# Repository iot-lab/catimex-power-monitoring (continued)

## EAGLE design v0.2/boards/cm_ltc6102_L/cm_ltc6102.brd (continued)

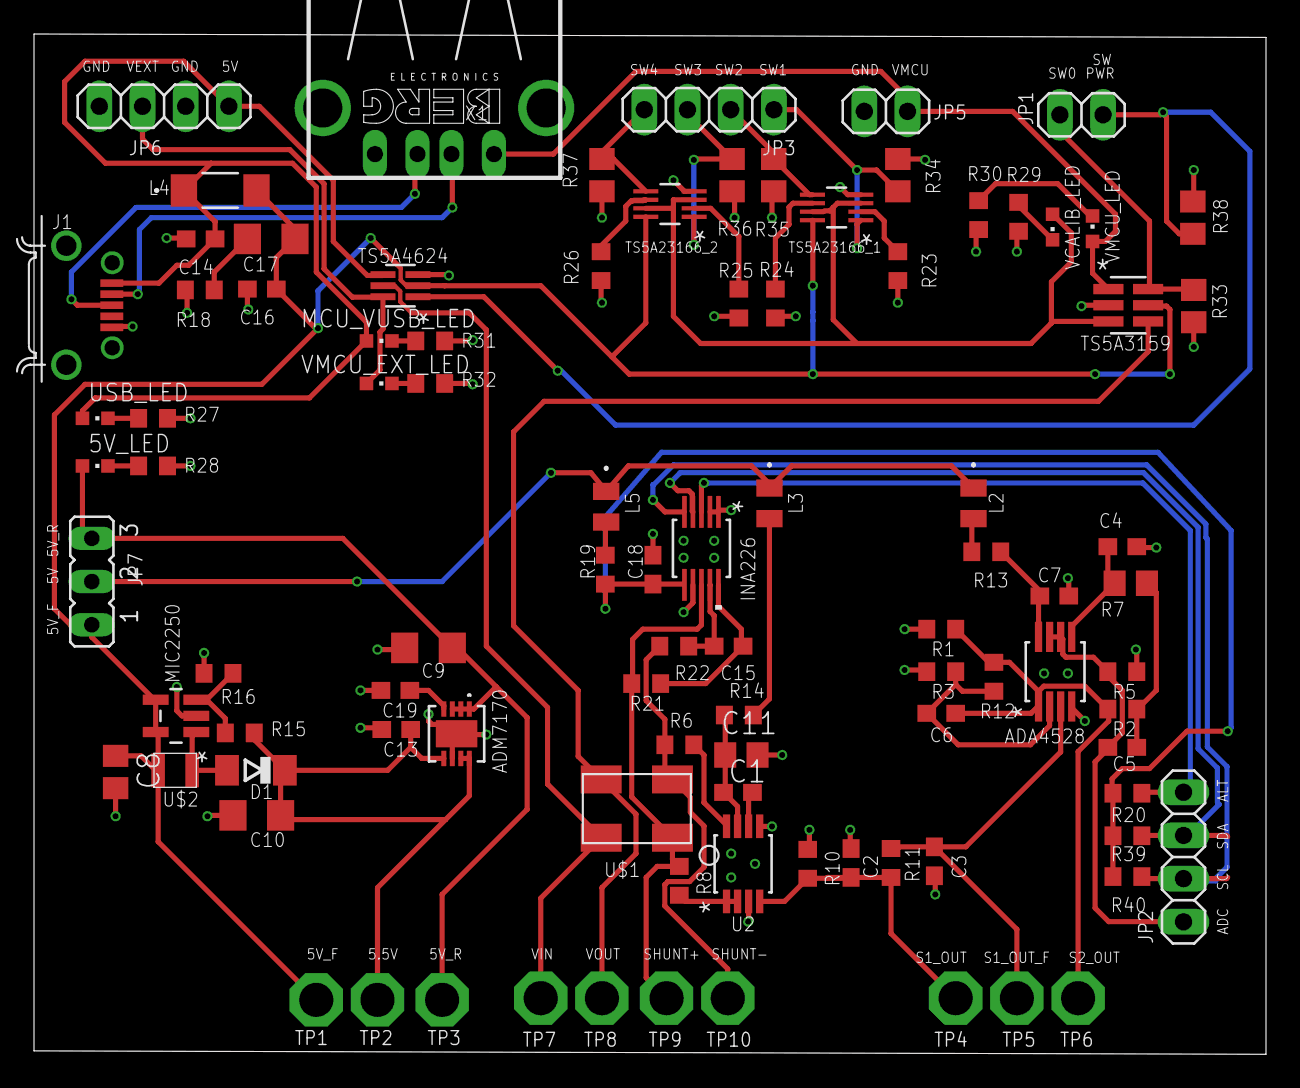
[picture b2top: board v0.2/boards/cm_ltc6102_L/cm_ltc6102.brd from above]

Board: 2 copper layers, 72.5 x 60.0 mm, 96 parts (1 on the bottom side), 57 nets.

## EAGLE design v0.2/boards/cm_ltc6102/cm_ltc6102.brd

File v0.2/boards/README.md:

# PCB eagle for current measurement board

This board contains the eagle files for current measurement board. It contains two options for the circuit:

* LTC6102 based circuit measurement
* ADA4522 based circuit measurement

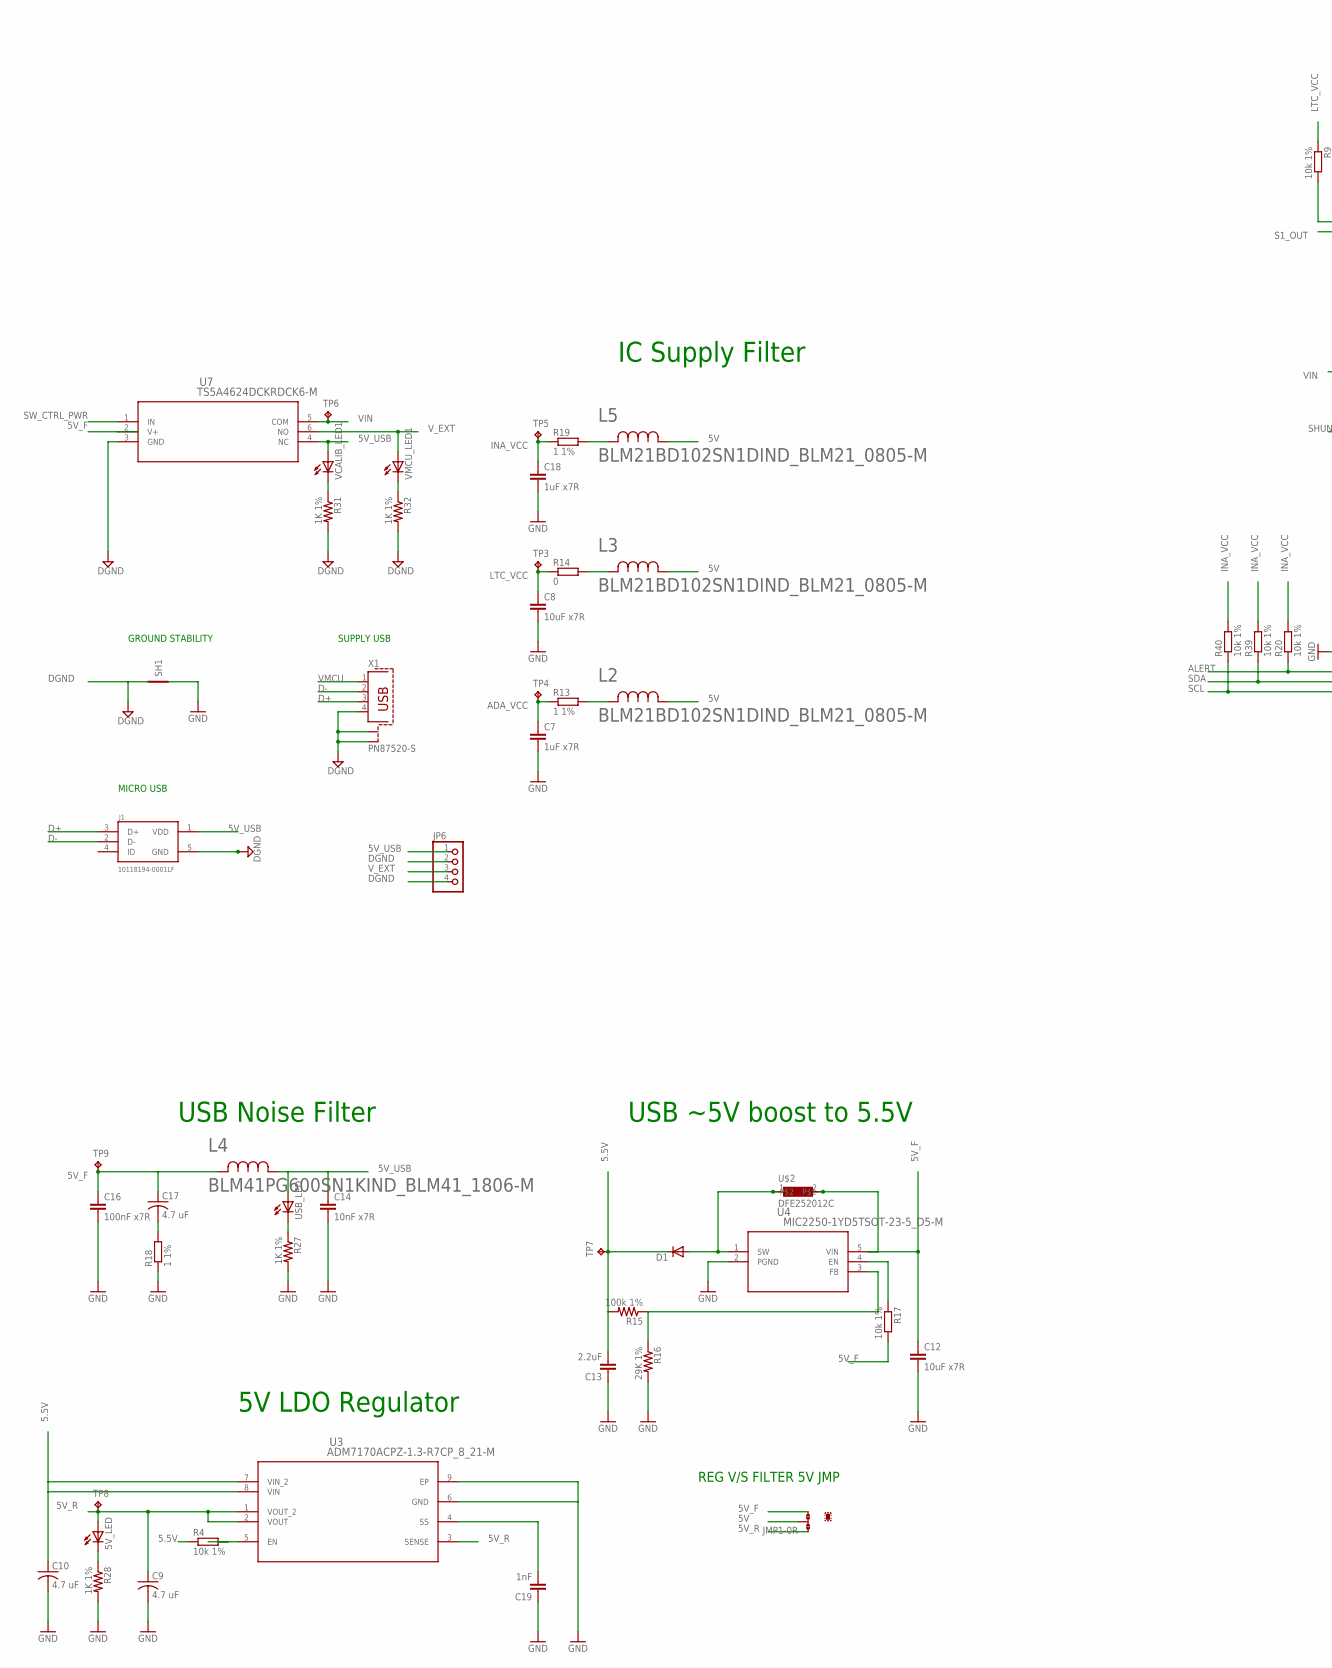
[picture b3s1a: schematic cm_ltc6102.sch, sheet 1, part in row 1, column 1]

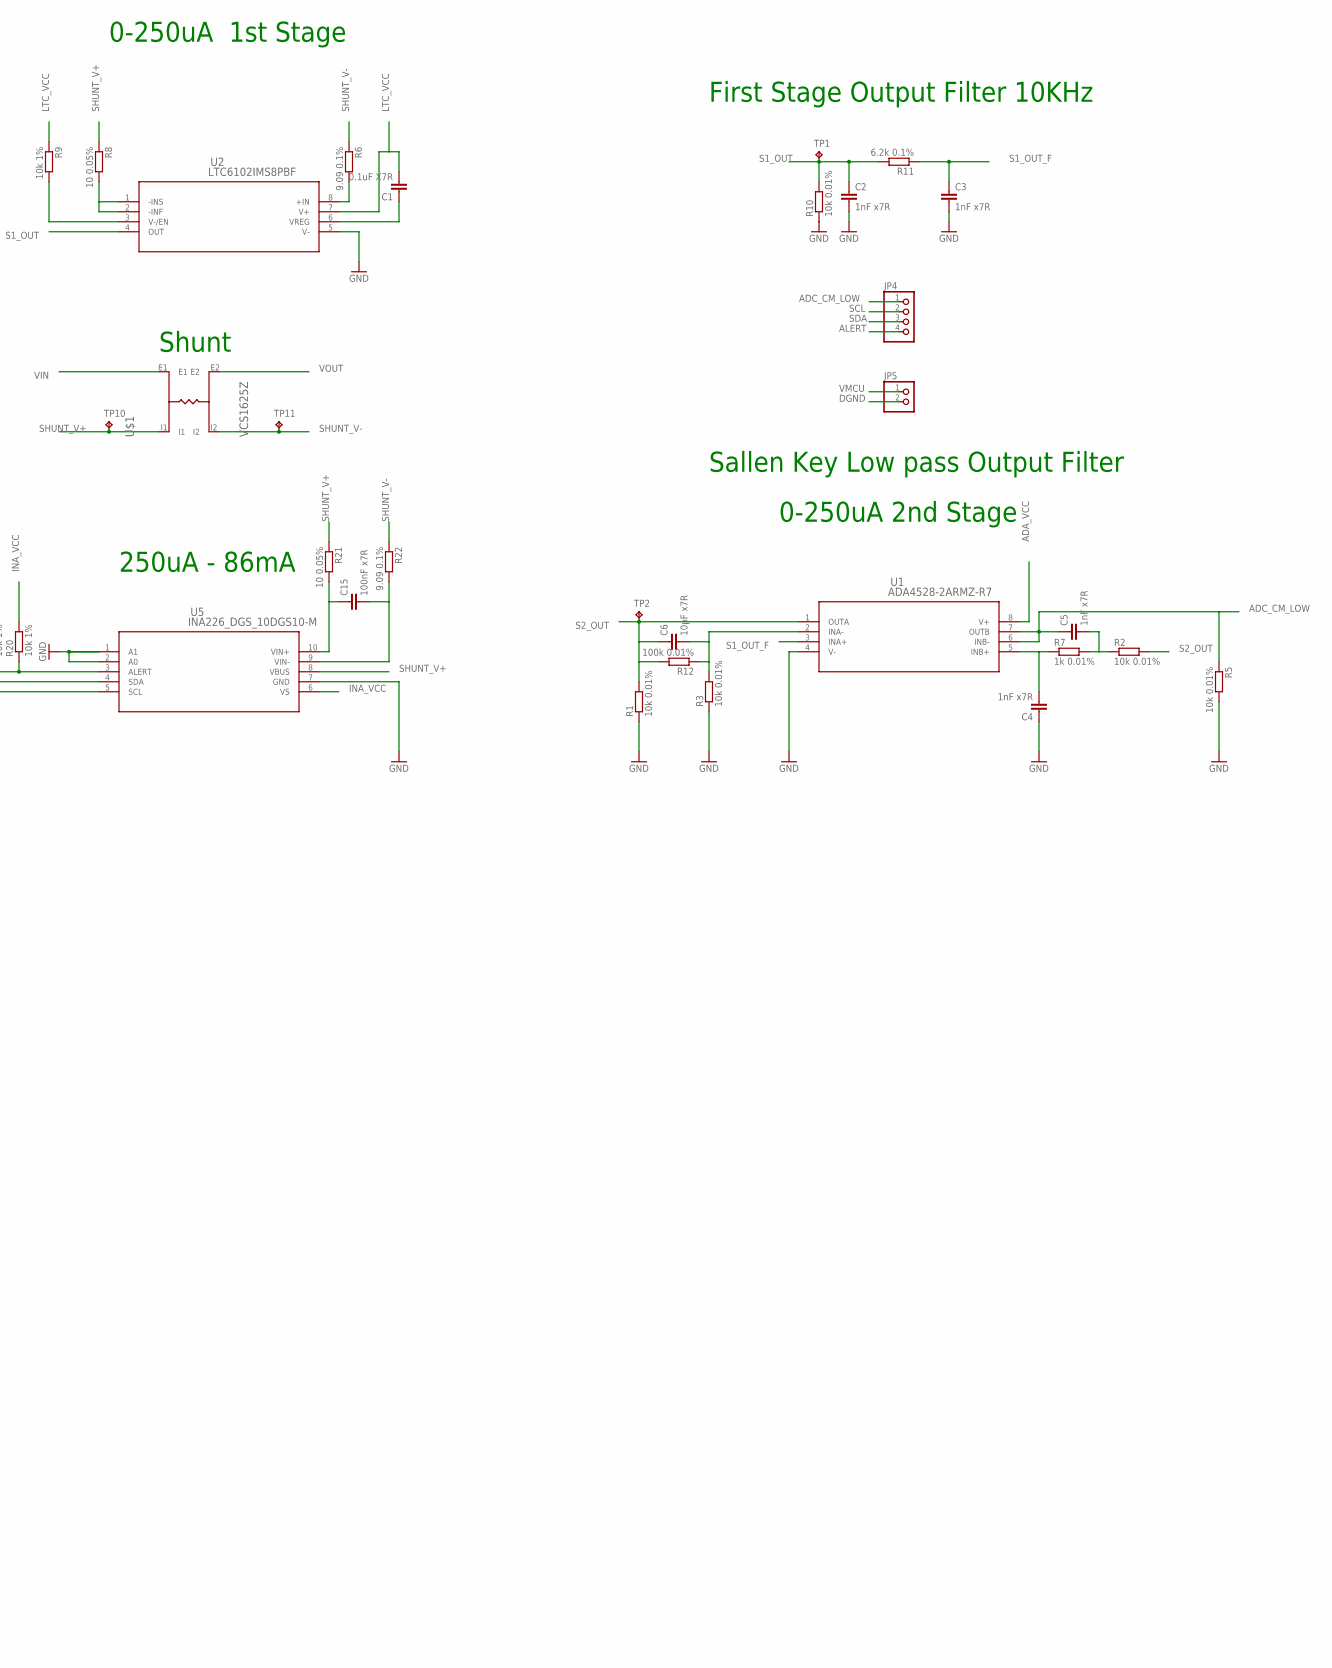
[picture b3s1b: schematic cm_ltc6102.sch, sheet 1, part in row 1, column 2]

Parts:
5V_LED: LEDCHIPLED_0603; CHIPLED_0603
C1: 0.1uF X7R; C0805
C2, C3, C4, C5: 1nF x7R; C0603
C6: 10pF x7R; C0603
C7, C18: 1uF x7R; C0603
C8, C12: 10uF x7R; C0603
C9, C10, C17: 4.7 uF; C1206
C13: 2.2uF; C0603
C14: 10nF x7R; C0603
C15, C16: 100nF x7R; C0603
C19: 1nF; C0603
D1: DIODE-SOD80C; SOD80C
J1: 10118194-0001LF; FRAMATOME_10118194-0001LF
JMP1: 0R-JUMPA; A0R-JMP
JP4, JP6: PINHD-1X4; 1X04
JP5: PINHD-1X2; 1X02
L2, L3, L5: BLM21BD102SN1DIND_BLM21_0805-M; IND_BLM21_0805-M
L4: BLM41PG600SN1KIND_BLM41_1806-M; IND_BLM41_1806-M
R1, R2, R3, R5, R10: 10k 0.01%; R0603
R4, R9, R17, R20, R39, R40: 10k 1%; R0603
R6, R22: 9.09 0.1%; R0603
R7: 1k 0.01%; R0805
R8, R21: 10 0.05%; R0603
R11: 6.2k 0.1%; R0603
R12: 100k 0.01%; R0603
R13, R18, R19: 1 1%; R0603
R14: 0; R0603
R15: 100k 1%; R0603
R16: 29K 1%; R0603
R27, R28, R31, R32: 1K 1%; R0603
SH1: SHORT-VT5; SHORT_TOP-50
TP1, TP2: TPPAD1-13; P1-13
TP3, TP4, TP5, TP6, TP7, TP8, TP9, TP10, TP11: TPTP11R; TP11R
U1: ADA4528-2ARMZ-R7; RM_8
U2: LTC6102IMS8PBF; MSOP-8_MS
U3: ADM7170ACPZ-1.3-R7CP_8_21-M; CP_8_21-M
U4: MIC2250-1YD5TSOT-23-5_D5-M; TSOT-23-5_D5-M
U5: INA226_DGS_10DGS10-M; DGS10-M
U7: TS5A4624DCKRDCK6-M; DCK6-M
U$1: VCS1625Z
U$2: DFE252012C
USB_LED: LEDCHIPLED_0603; CHIPLED_0603
VCALIB_LED1: LEDCHIPLED_0603; CHIPLED_0603
VMCU_LED1: LEDCHIPLED_0603; CHIPLED_0603
X1: PN87520-S

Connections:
5.5V: C10.1, C13.2, D1.C, R4.1, R15.2, TP7.TP, U3.7 (VIN_2), U3.8 (VIN)
5V: JMP1.2, L2.1, L3.1, L5.1
5V_F: C12.1, C16.1, C17.1, JMP1.3, L4.2, R17.2, TP9.TP, U4.5 (VIN), U7.2 (V+), U$2.2; also elsewhere on the board
5V_R: 5V_LED.A, C9.1, JMP1.1, TP8.TP, U3.1 (VOUT_2), U3.2 (VOUT), U3.3 (SENSE)
5V_USB: C14.1, J1.1 (VDD), JP6.1, L4.1, U7.4 (NC), USB_LED.A, VCALIB_LED1.A
ADA_VCC: C7.1, R13.1, TP4.TP, U1.8 (V+)
ADC_CM_LOW: C5.1, JP4.1, R5.1, U1.6 (INB-), U1.7 (OUTB)
ALERT: JP4.4, R20.1, U5.3 (ALERT)
D+: J1.3 (D+), X1.3
D-: J1.2 (D-), X1.2
DGND: J1.5 (GND), JP5.2, JP6.2, JP6.4, R31.2, R32.2, SH1.2, U7.3 (GND), X1.4, X1.S1, X1.S2; also elsewhere on the board
GND: C2.2, C3.2, C4.1, C7.2, C8.2, C9.2, C10.2, C12.2, C13.1, C14.2, C16.2, C18.2, C19.1, R1.1, R3.1, R5.2, R10.1, R16.2, R18.1, R27.2, R28.2, SH1.1, U1.4 (V-), U2.5 (V-), U3.6 (GND), U3.9 (EP), U4.2 (PGND), U5.1 (A1), U5.2 (A0), U5.7 (GND)
INA_VCC: C18.1, R19.1, R20.2, R39.2, R40.2, TP5.TP, U5.6 (VS)
LTC_VCC: C1.2, C8.1, R9.1, R14.1, TP3.TP, U2.7 (V+)
unnamed: R8.2, U2.1 (-INS), U2.2 (-INF)
unnamed: R6.2, U2.8 (+IN)
unnamed: R27.1, USB_LED.C
unnamed: R9.2, U2.3 (V-/EN)
unnamed: C1.1, U2.6 (VREG)
unnamed: C4.2, R7.1, U1.5 (INB+)
unnamed: C5.2, R2.1, R7.2
unnamed: L3.2, R14.2
unnamed: D1.A, U4.1 (SW), U$2.1
unnamed: C6.2, R3.2, R12.1, U1.2 (INA-)
unnamed: L2.2, R13.2
unnamed: C15.1, R21.2, U5.10 (VIN+)
unnamed: C19.2, U3.4 (SS)
unnamed: R4.2, U3.5 (EN)
unnamed: R15.1, R16.1, U4.3 (FB)
unnamed: R17.1, U4.4 (EN)
unnamed: C17.2, R18.2
unnamed: L5.2, R19.2
unnamed: C15.2, R22.2, U5.9 (VIN-)
unnamed: 5V_LED.C, R28.1
unnamed: R31.1, VCALIB_LED1.C
unnamed: R32.1, VMCU_LED1.C
S1_OUT: C2.1, R10.2, R11.2, TP1.TP, U2.4 (OUT)
S1_OUT_F: C3.1, R11.1, U1.3 (INA+)
S2_OUT: C6.1, R1.2, R2.2, R12.2, TP2.TP, U1.1 (OUTA)
SCL: JP4.2, R40.1, U5.5 (SCL)
SDA: JP4.3, R39.1, U5.4 (SDA)
SHUNT_V+: R8.1, R21.1, TP10.TP, U5.8 (VBUS), U$1.I1
SHUNT_V-: R6.1, R22.1, TP11.TP, U$1.I2
SW_CTRL_PWR: U7.1 (IN); also elsewhere on the board
VIN: TP6.TP, U7.5 (COM), U$1.E1
VMCU: JP5.1, X1.1; also elsewhere on the board
VOUT: U$1.E2; also elsewhere on the board
V_EXT: JP6.3, U7.6 (NO), VMCU_LED1.A

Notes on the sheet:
USB Noise Filter
USB ~5V boost to 5.5V
5V LDO Regulator
IC Supply Filter
First Stage Output Filter 10KHz
Sallen Key Low pass Output Filter
0-250uA 2nd Stage
0-250uA 1st Stage
250uA - 86mA
Shunt
SUPPLY USB
MICRO USB
GROUND STABILITY
REG V/S FILTER 5V JMP

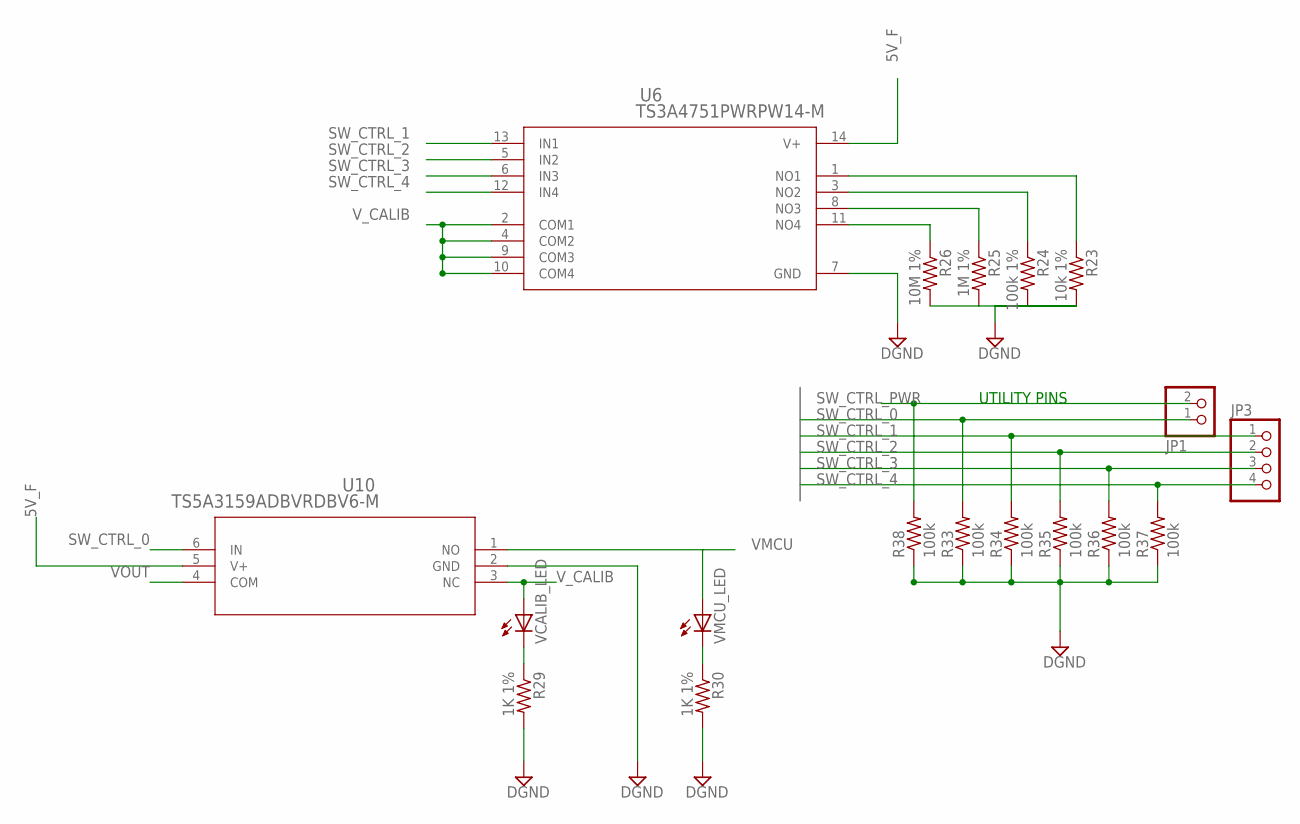
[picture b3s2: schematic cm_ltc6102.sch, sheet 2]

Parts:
JP1: PINHD-1X2; 1X02
JP3: PINHD-1X4; 1X04
R23: 10k 1%; R0603
R24: 100k 1%; R0603
R25: 1M 1%; R0603
R26: 10M 1%; R0603
R29, R30: 1K 1%; R0603
R33, R34, R35, R36, R37, R38: 100k; R0805
U6: TS3A4751PWRPW14-M; PW14-M
U10: TS5A3159ADBVRDBV6-M; DBV6-M
VCALIB_LED: LEDCHIPLED_0603; CHIPLED_0603
VMCU_LED: LEDCHIPLED_0603; CHIPLED_0603

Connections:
5V_F: U6.14 (V+), U10.5 (V+); also elsewhere on the board
DGND: R23.2, R24.2, R25.2, R26.2, R29.2, R30.2, R33.1, R34.1, R35.1, R36.1, R37.1, R38.1, U6.7 (GND), U10.2 (GND); also elsewhere on the board
unnamed: R29.1, VCALIB_LED.C
unnamed: R30.1, VMCU_LED.C
unnamed: R23.1, U6.1 (NO1)
unnamed: R24.1, U6.3 (NO2)
unnamed: R25.1, U6.8 (NO3)
unnamed: R26.1, U6.11 (NO4)
SW_CTRL_0: JP1.1, R33.2, U10.6 (IN)
SW_CTRL_1: JP3.1, R34.2, U6.13 (IN1)
SW_CTRL_2: JP3.2, R35.2, U6.5 (IN2)
SW_CTRL_3: JP3.3, R36.2, U6.6 (IN3)
SW_CTRL_4: JP3.4, R37.2, U6.12 (IN4)
SW_CTRL_PWR: JP1.2, R38.2; also elsewhere on the board
VMCU: U10.1 (NO), VMCU_LED.A; also elsewhere on the board
VOUT: U10.4 (COM); also elsewhere on the board
V_CALIB: U6.2 (COM1), U6.4 (COM2), U6.9 (COM3), U6.10 (COM4), U10.3 (NC), VCALIB_LED.A

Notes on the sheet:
UTILITY PINS

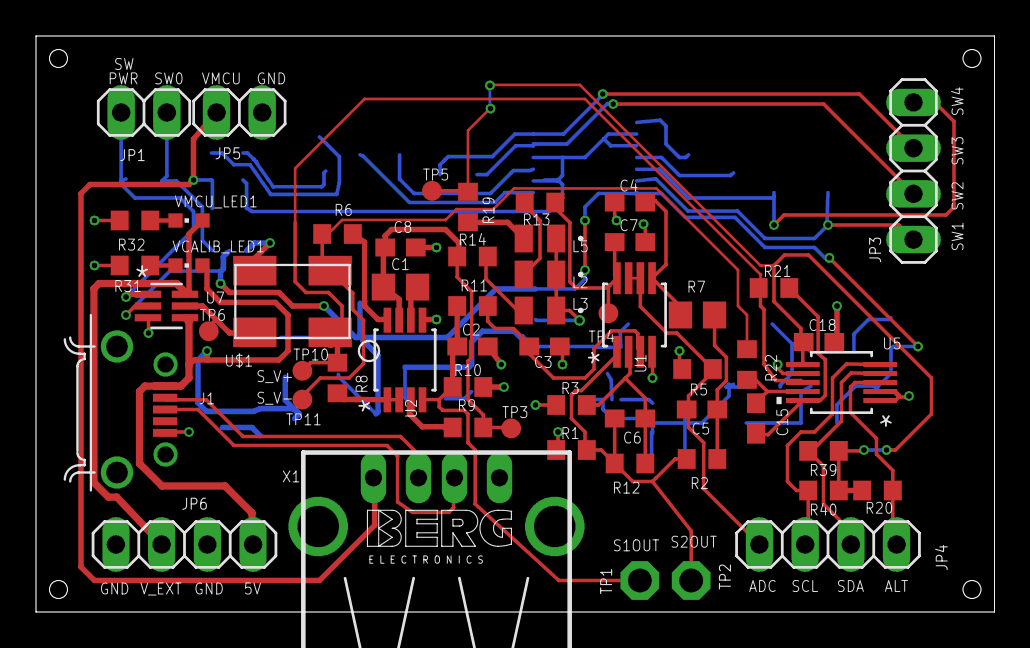
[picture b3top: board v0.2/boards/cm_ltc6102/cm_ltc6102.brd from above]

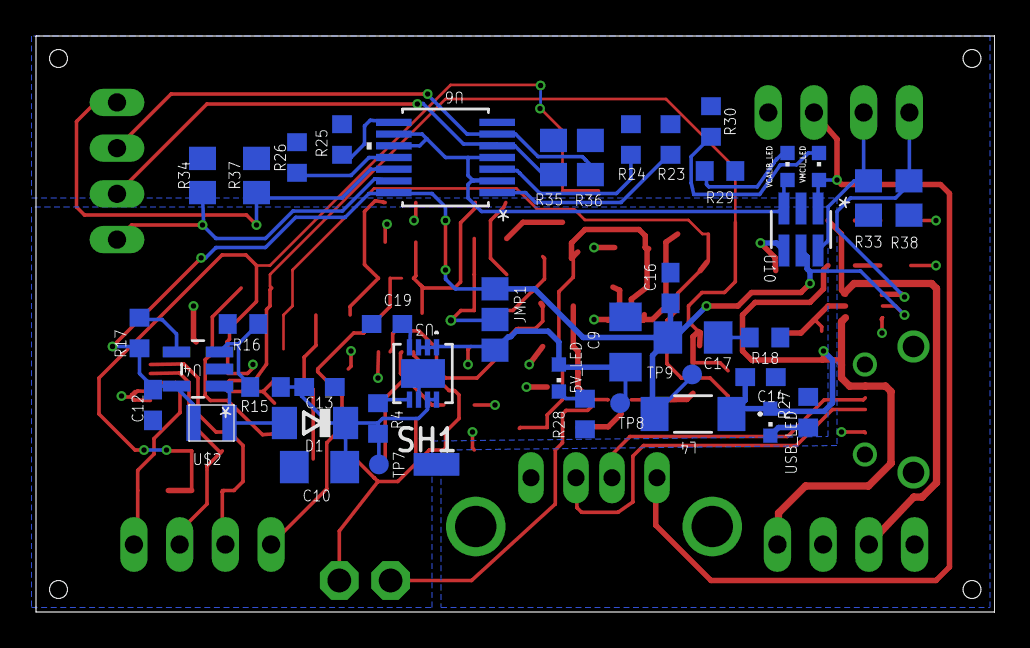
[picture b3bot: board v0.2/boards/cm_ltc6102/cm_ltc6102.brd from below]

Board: 2 copper layers, 53.2 x 32.0 mm, 99 parts (43 on the bottom side), 60 nets.

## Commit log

2018-02-14 add nucleo-l152 support
2018-02-14 create serial_port.py to control measure_node
2018-02-14 add calibrate func
2018-02-14 wip on transforming read values
2018-02-19 add start_reading function, proper testing pending
2018-02-19 add requirements for python env
2018-03-15 fix error in adc resolution setting function
2018-03-22 move first iteration to v0.1 folder
2018-03-23 add non asc spice files to gitignore
2018-03-23 add v.02 A & B solution with LTC6102
2018-03-26 remove unvalid designs
2018-03-26 add base spice design for ada4522 base circuit
2018-03-28 update schematics
2018-03-28 initial work on pcb eagle
2018-04-04 add folder to spice models
2018-04-05 first circuit for AD8629
2018-04-09 add AD8422 for large current measurement - change power supply
2018-04-09 fix power supply for ad8629
2018-04-10 pcb: add eagle symbols
2018-04-10 boards: add initial version for ltc6102 based board
2018-04-11 cm_ltc6102: add dgnd and agnd connection, fix silk-screen
2018-04-13 fix some missing gnd wires
2018-04-13 add larger version of ltc6102 based board
    same ics different board size
2018-04-13 create measure-circuit to eagle sch
2018-04-16 cm_ltc6102_L: modify layout, finish silkscreen
2018-04-16 cm_ltc6102_L: fix wrong sized ic and surface capacitor
2018-04-16 add bom
2018-04-17 add analog switch eagle symbol
2018-04-17 add 12v boost to sch
2018-04-17 add 12v boost power supply
2018-04-18 add regulator and boost
2018-04-18 add usb entry
2018-04-18 fix enable pull ups error, update bom
2018-04-20 fix minor issues
2018-04-20 add layout board
2018-04-20 add boom file
2018-04-20 fix issues
2018-04-20 first version of layout
    add bom file
    fix issues
2018-04-20 add usb ports to schematics
2018-04-20 fix ltspice symbol orientation
2018-04-20 cm_ltc6102: increase track size add doc
2018-04-23 change AD8629 to ADA4522
2018-04-23 ltc6102_board: change silscreen names to top silkscreen
2018-04-23 ltc6102_board: minor board fixes
2018-04-23 connect data ports from usb
2018-04-23 add bom to folder
2018-04-23 add names to external connectors
2018-05-02 move v0.2 files to common folder
2018-05-02 update common board readme
2018-05-02 add ltc6102 bom
2018-05-02 update bom for ada4522
2018-05-23 update board readme
2018-06-15 add schematic file as pdf
2018-06-15 add schematic pdf file to ada board
2018-08-27 Add version 3 of hardware: include control node and usb bridge in design
2018-09-10 Add README to v0.3 hardware
2018-09-10 Update README to mention jumper placement
2018-10-09 Fix bugs v0.3
2018-10-17 change R14 Digikey Part Number to 0805 footprint
2018-12-18 Readme: Add connectors information and pinout
2019-06-05 Relocate hardware files
2019-06-05 Update missing features to Readme
2022-06-21 Bump numpy from 1.14.0 to 1.22.0 in /legacy/v0.1/scripts/power_measure
    Bumps [numpy](https://github.com/numpy/numpy) from 1.14.0 to 1.22.0.
    - [Release notes](https://github.com/numpy/numpy/releases)
    - [Changelog](https://github.com/numpy/numpy/blob/main/doc/HOWTO_RELEASE.rst)
    - [Commits](https://github.com/numpy/numpy/compare/v1.14.0...v1.22.0)
    ---
    updated-dependencies:
